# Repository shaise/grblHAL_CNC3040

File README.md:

# grblHAL_CNC3040 [WIP]
Hardware implementation of the grblHAL driver to work with Chinese CNC3040 type of machines  

This project is intended to upgrade any cnc machine that is controlled via parallel port such as the popular chinese CNC3040.  
Instead of having a dedicated LinuxCNC PC or mach32, This device connects directly to the CNC's controller, and can be controlled using any grbl Sender sw via USB connection or even WiFi!  
This device supports an optional stand-alone KeyPad, that is also included in this project.  

This project is based on the great work of @terjeio and his [GrblHAL](https://github.com/grblHAL) project. Thanks!

## Some images:

## Driver and KeyPad Assembly:
For instructions how to assemble, program and use the devices refer to the Wiki.

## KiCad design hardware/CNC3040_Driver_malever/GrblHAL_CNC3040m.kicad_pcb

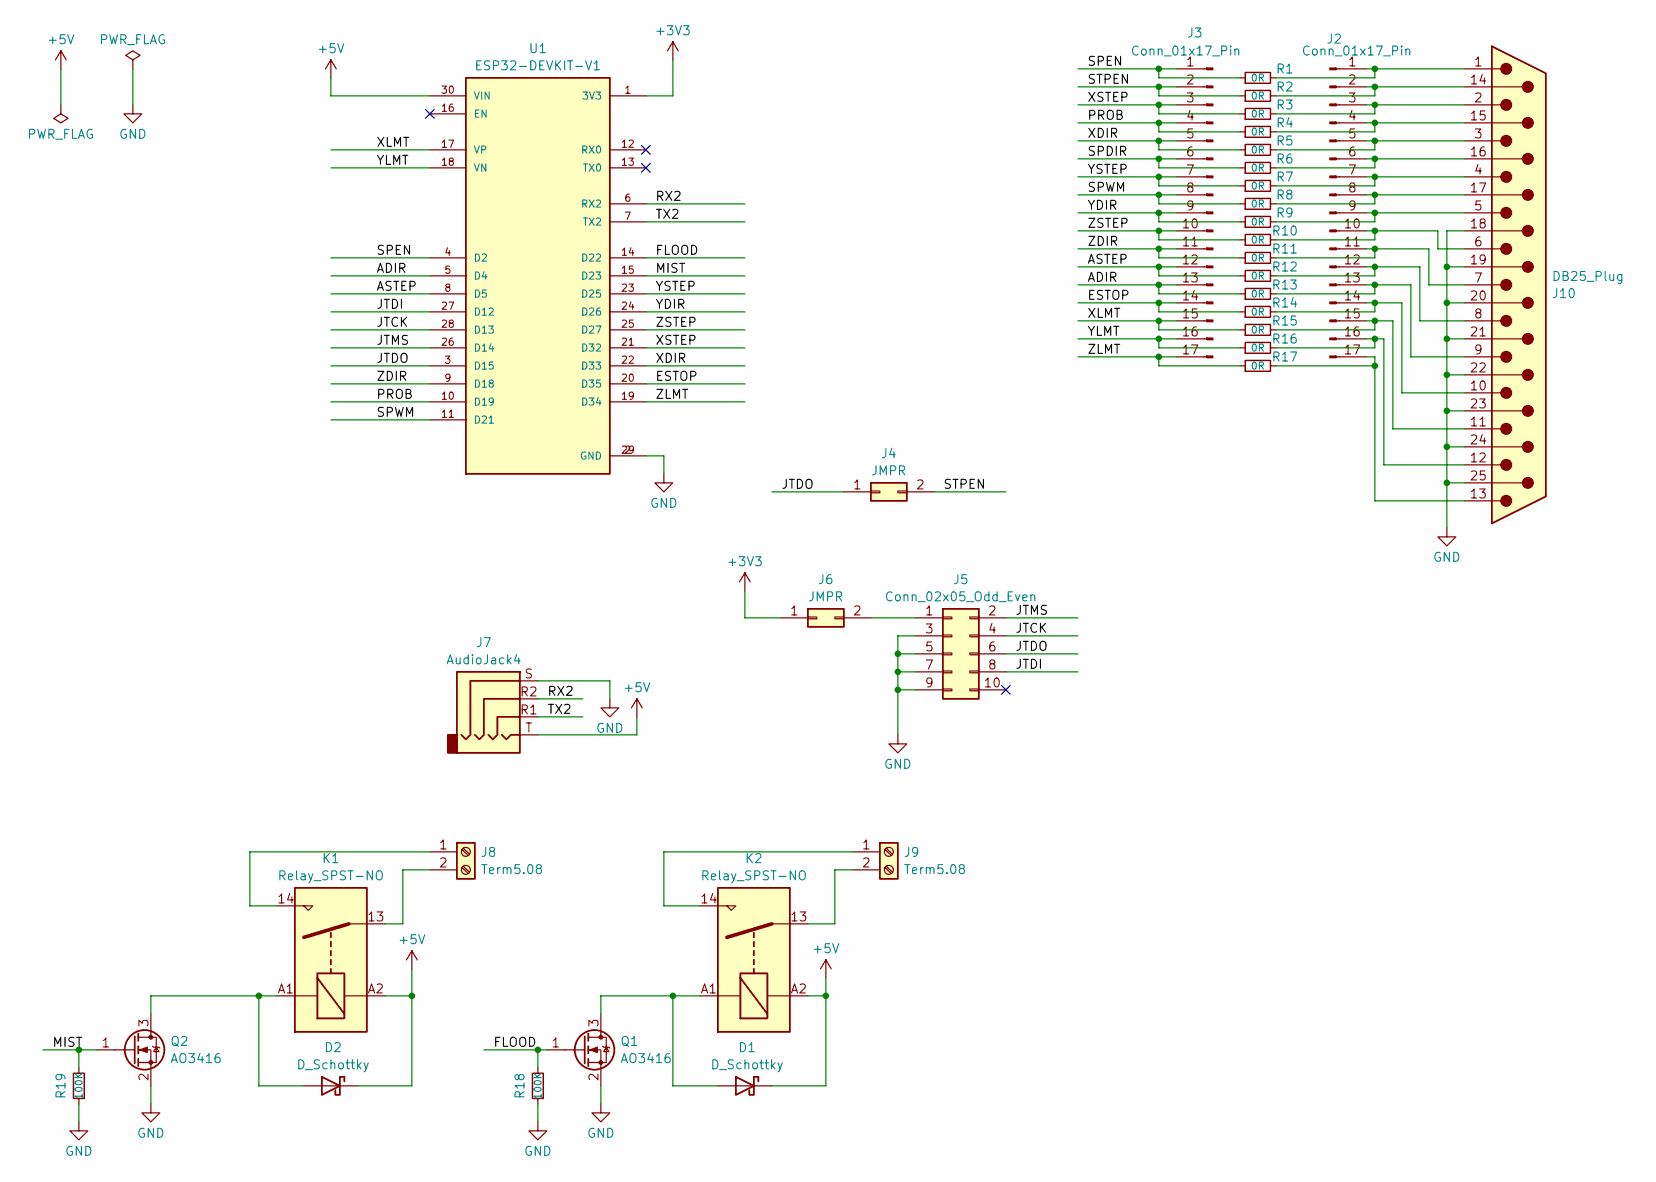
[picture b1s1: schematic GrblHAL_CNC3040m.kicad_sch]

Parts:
D1, D2: D_Schottky; D_SMA
J2, J3: Conn_01x17_Pin; PinHeader_1x17_P2.54mm_Vertical
J4, J6: JMPR; PinHeader_1x02_P2.54mm_Vertical
J5: Conn_02x05_Odd_Even; IDC-Header_2x05_P2.54mm_Vertical
J7: AudioJack4; Jack_3.5mm_PJ-320A
J8, J9: Term5.08; TerminalBlock_Phoenix_MKDS-1,5-2-5.08_1x02_P5.08mm_Horizont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
J10: DB25_Plug; DSUB-25_Male_Horizontal_P2.77x2.84mm_EdgePinOffset4.94mm_Ho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
K1, K2: Relay_SPST-NO; Relay_HF32FV-G
Q1, Q2: AO3416; SOT-23-3
R1, R2, R3, R4, R5, R6, R7, R8, R9, R10, R11, R12, R13, R14, R15, R16, R17: 0R; R_0603_1608Metric
R18, R19: 100K; R_0603_1608Metric
U1: ESP32-DEVKIT-V1; MODULE_ESP32_DEVKIT_V1; PARTREV N/A

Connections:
+3V3: J6.1, U1.1 (3V3)
+5V: D1.1 (K), D2.1 (K), J7.T, K1.A2, K2.A2, U1.30 (VIN)
/ADIR: J3.13, R13.1, U1.5 (D4)
/ASTEP: J3.12, R12.1, U1.8 (D5)
/ESTOP: J3.14, R14.1, U1.20 (D35)
/FLOOD: Q1.1 (G), R18.2, U1.14 (D22)
/JTCK: J5.4, U1.28 (D13)
/JTDI: J5.8, U1.27 (D12)
/JTDO: J4.1, J5.6, U1.3 (D15)
/JTMS: J5.2, U1.26 (D14)
/MIST: Q2.1 (G), R19.2, U1.15 (D23)
/PROB: J3.4, R4.1, U1.10 (D19)
/RX2: J7.R2, U1.6 (RX2)
/SPDIR: J3.6, R6.1
/SPEN: J3.1, R1.1, U1.4 (D2)
/SPWM: J3.8, R8.1, U1.11 (D21)
/STPEN: J3.2, J4.2, R2.1
/TX2: J7.R1, U1.7 (TX2)
/XDIR: J3.5, R5.1, U1.22 (D33)
/XLMT: J3.15, R15.1, U1.17 (VP)
/XSTEP: J3.3, R3.1, U1.21 (D32)
/YDIR: J3.9, R9.1, U1.24 (D26)
/YLMT: J3.16, R16.1, U1.18 (VN)
/YSTEP: J3.7, R7.1, U1.23 (D25)
/ZDIR: J3.11, R11.1, U1.9 (D18)
/ZLMT: J3.17, R17.1, U1.19 (D34)
/ZSTEP: J3.10, R10.1, U1.25 (D27)
GND: J5.3, J5.5, J5.7, J5.9, J7.S, J10.18, J10.19, J10.20, J10.21, J10.22, J10.23, J10.24, J10.25, Q1.2 (S), Q2.2 (S), R18.1, R19.1, U1.2 (GND), U1.29 (GND)
unnamed: D1.2 (A), K2.A1, Q1.3 (D)
unnamed: D2.2 (A), K1.A1, Q2.3 (D)
unnamed: J2.1, J10.1, R1.2
unnamed: J2.3, J10.2, R3.2
unnamed: J2.5, J10.3, R5.2
unnamed: J2.7, J10.4, R7.2
unnamed: J2.9, J10.5, R9.2
unnamed: J2.10, J10.6, R10.2
unnamed: J2.11, J10.7, R11.2
unnamed: J2.12, J10.8, R12.2
unnamed: J2.13, J10.9, R13.2
unnamed: J2.14, J10.10, R14.2
unnamed: J2.15, J10.11, R15.2
unnamed: J2.16, J10.12, R16.2
unnamed: J2.17, J10.13, R17.2
unnamed: J5.1, J6.2
unnamed: J8.1, K1.14
unnamed: J8.2, K1.13
unnamed: J9.1, K2.14
unnamed: J9.2, K2.13
unnamed: J2.2, J10.14, R2.2
unnamed: J2.4, J10.15, R4.2
unnamed: J2.6, J10.16, R6.2
unnamed: J2.8, J10.17, R8.2

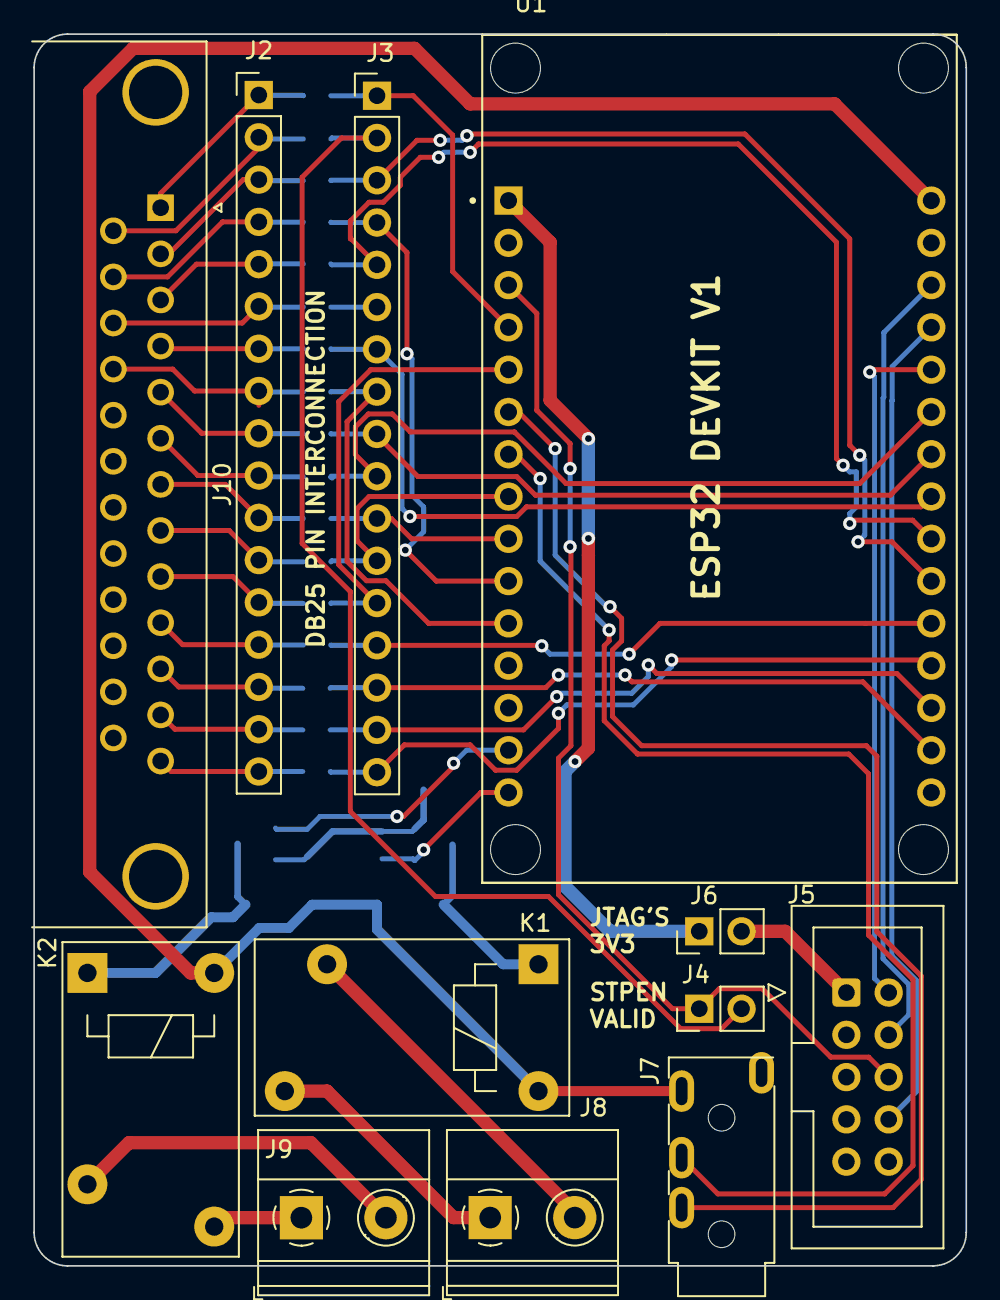
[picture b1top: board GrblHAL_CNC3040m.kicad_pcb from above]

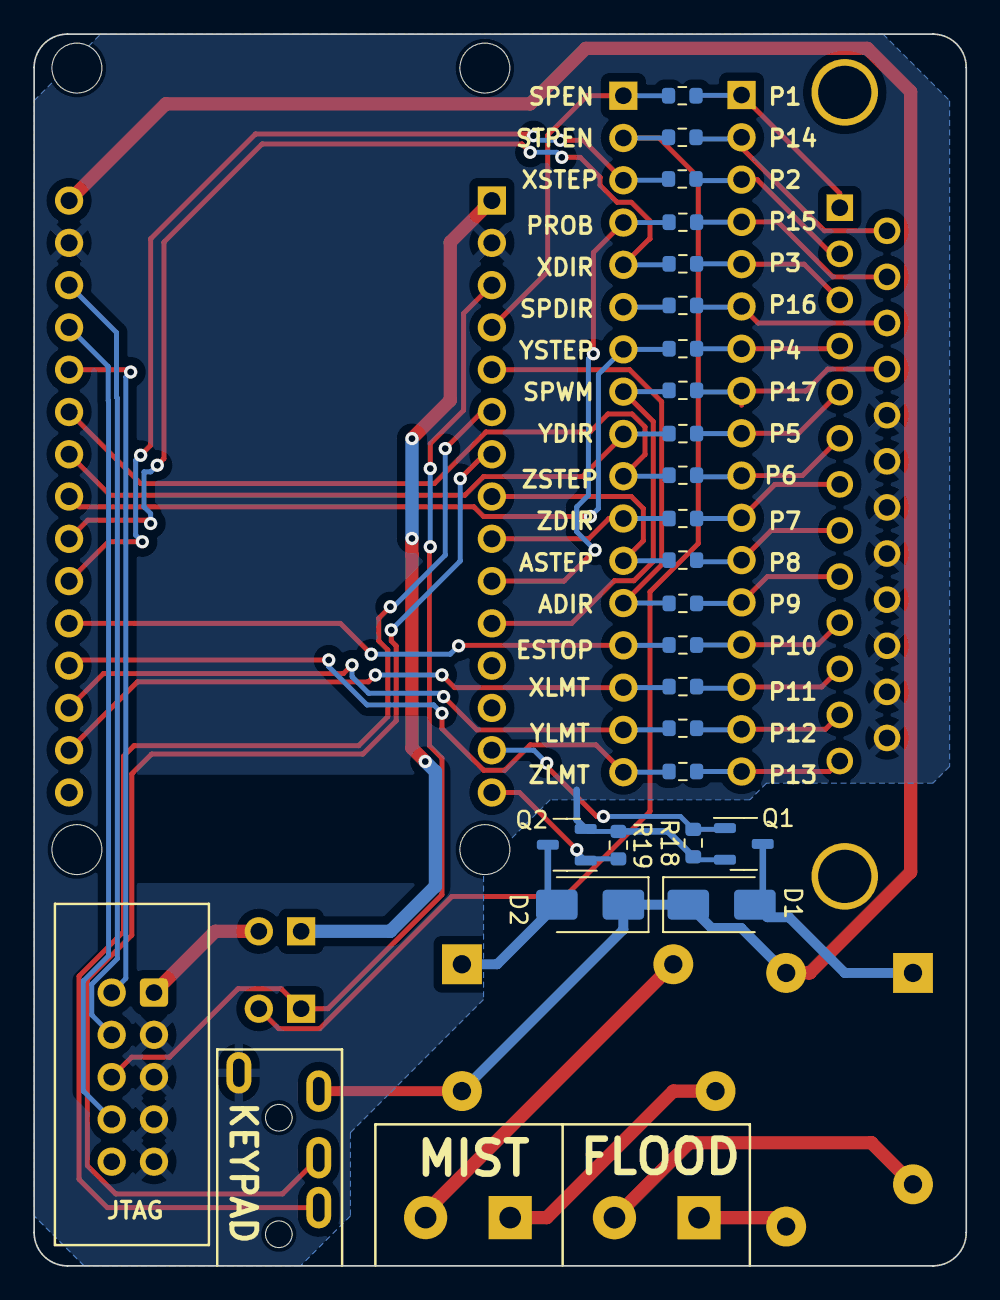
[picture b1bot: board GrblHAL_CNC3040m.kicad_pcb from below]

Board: 2 copper layers, 56.0 x 74.0 mm, 35 parts (23 on the bottom side), 52 nets.

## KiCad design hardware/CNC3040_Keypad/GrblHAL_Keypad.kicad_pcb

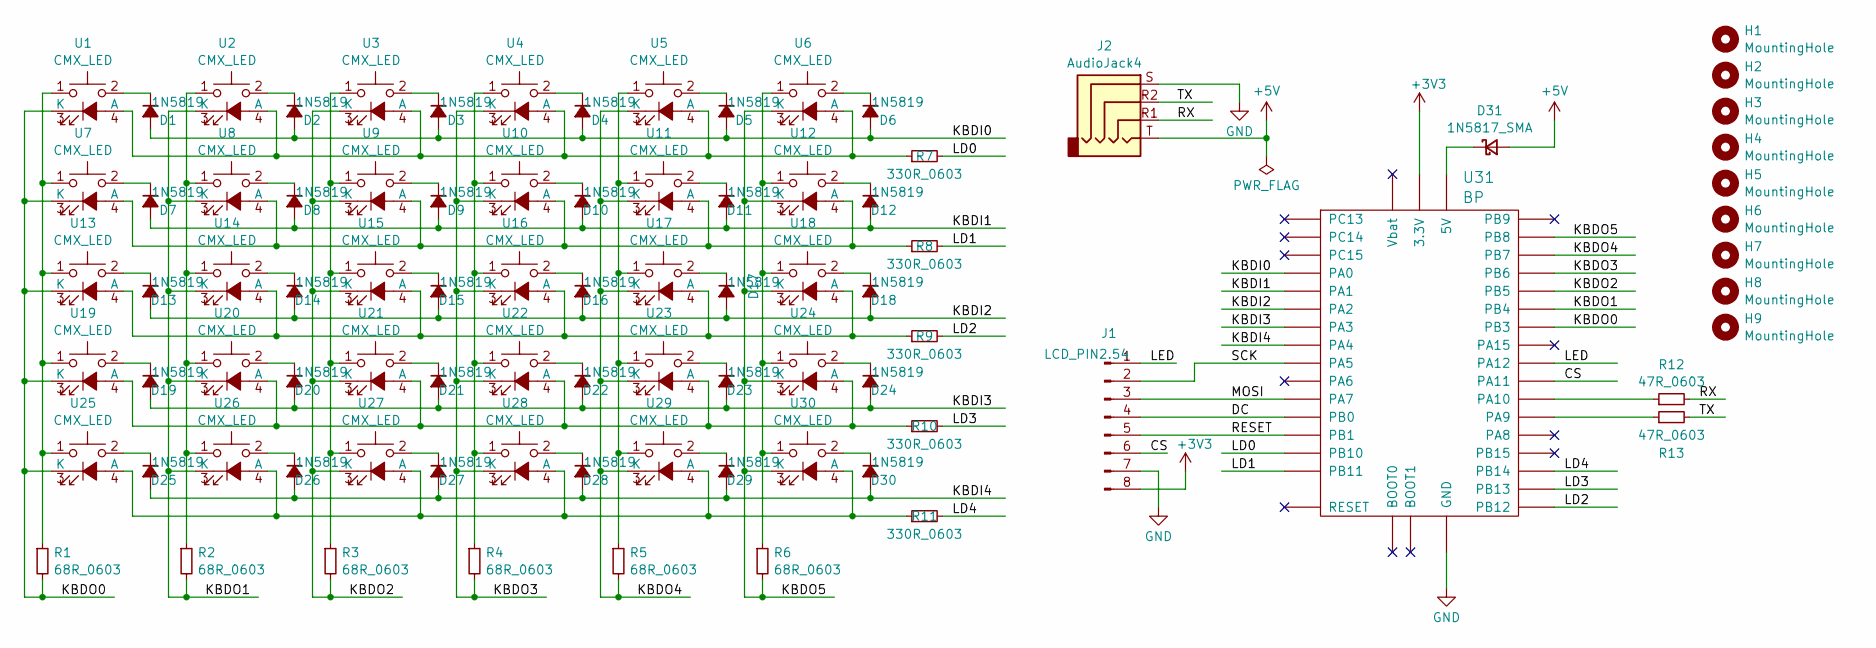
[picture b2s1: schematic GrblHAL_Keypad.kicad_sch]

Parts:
D1, D2, D3, D4, D5, D6, D7, D8, D9, D10, D11, D12, D13, D14, D15, D16, D17, D18, D19, D20, D21, D22, D23, D24, D25, D26, D27, D28, D29, D30: 1N5819; D_SOD-123
D31: 1N5817_SMA; D_SMA
H1, H2, H3, H4, H5, H6, H7, H8, H9: MountingHole; MountingHole_3.2mm_M3
J1: LCD_PIN2.54; PinHeader_1x08_P2.54mm_Vertical
J2: AudioJack4; Jack_3.5mm_PJ-320A
R1, R2, R3, R4, R5, R6: 68R_0603; R_0603_1608Metric
R7, R8, R9, R10, R11: 330R_0603; R_0603_1608Metric
R12, R13: 47R_0603; R_0603_1608Metric
U1, U2, U3, U4, U5, U6, U7, U8, U9, U10, U11, U12, U13, U14, U15, U16, U17, U18, U19, U20, U21, U22, U23, U24, U25, U26, U27, U28, U29, U30: CMX_LED; CherryMX_1.00u_KailhSocket_LED
U31: BP; BLUEPILL-BARE

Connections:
+3V3: J1.8, U31.3V3 (3.3V)
+5V: D31.2 (A), J2.T
/CS: J1.6, U31.PA11
/DC: J1.4, U31.PB0
/KBDI0: D1.2 (A), D2.2 (A), D3.2 (A), D4.2 (A), D5.2 (A), D6.2 (A), U31.PA0
/KBDI1: D7.2 (A), D8.2 (A), D9.2 (A), D10.2 (A), D11.2 (A), D12.2 (A), U31.PA1
/KBDI2: D13.2 (A), D14.2 (A), D15.2 (A), D16.2 (A), D17.2 (A), D18.2 (A), U31.PA2
/KBDI3: D19.2 (A), D20.2 (A), D21.2 (A), D22.2 (A), D23.2 (A), D24.2 (A), U31.PA3
/KBDI4: D25.2 (A), D26.2 (A), D27.2 (A), D28.2 (A), D29.2 (A), D30.2 (A), U31.PA4
/KBDO0: R1.2, U1.3 (K), U7.3 (K), U13.3 (K), U19.3 (K), U25.3 (K), U31.PB3
/KBDO1: R2.2, U2.3 (K), U8.3 (K), U14.3 (K), U20.3 (K), U26.3 (K), U31.PB4
/KBDO2: R3.2, U3.3 (K), U9.3 (K), U15.3 (K), U21.3 (K), U27.3 (K), U31.PB5
/KBDO3: R4.2, U4.3 (K), U10.3 (K), U16.3 (K), U22.3 (K), U28.3 (K), U31.PB6
/KBDO4: R5.2, U5.3 (K), U11.3 (K), U17.3 (K), U23.3 (K), U29.3 (K), U31.PB7
/KBDO5: R6.2, U6.3 (K), U12.3 (K), U18.3 (K), U24.3 (K), U30.3 (K), U31.PB8
/LD0: R7.2, U31.PB10
/LD1: R8.2, U31.PB11
/LD2: R9.2, U31.PB12
/LD3: R10.2, U31.PB13
/LD4: R11.2, U31.PB14
/LED: J1.1, U31.PA12
/MOSI: J1.3, U31.PA7
/RESET: J1.5, U31.PB1
/RX: J2.R1, R12.2
/SCK: J1.2, U31.PA5
/TX: J2.R2, R13.2
GND: J1.7, J2.S, U31.G (GND)
unnamed: D1.1 (K), U1.2
unnamed: D2.1 (K), U2.2
unnamed: D3.1 (K), U3.2
unnamed: D4.1 (K), U4.2
unnamed: D5.1 (K), U5.2
unnamed: D6.1 (K), U6.2
unnamed: D7.1 (K), U7.2
unnamed: D8.1 (K), U8.2
unnamed: D9.1 (K), U9.2
unnamed: D10.1 (K), U10.2
unnamed: D11.1 (K), U11.2
unnamed: D12.1 (K), U12.2
unnamed: D13.1 (K), U13.2
unnamed: D14.1 (K), U14.2
unnamed: D15.1 (K), U15.2
unnamed: D16.1 (K), U16.2
unnamed: D17.1 (K), U17.2
unnamed: D18.1 (K), U18.2
unnamed: D19.1 (K), U19.2
unnamed: D20.1 (K), U20.2
unnamed: D21.1 (K), U21.2
unnamed: D22.1 (K), U22.2
unnamed: D23.1 (K), U23.2
unnamed: D24.1 (K), U24.2
unnamed: D25.1 (K), U25.2
unnamed: D26.1 (K), U26.2
unnamed: D27.1 (K), U27.2
unnamed: D28.1 (K), U28.2
unnamed: D29.1 (K), U29.2
unnamed: D30.1 (K), U30.2
unnamed: D31.1 (K), U31.5V
unnamed: R1.1, U1.1, U7.1, U13.1, U19.1, U25.1
unnamed: R2.1, U2.1, U8.1, U14.1, U20.1, U26.1
unnamed: R3.1, U3.1, U9.1, U15.1, U21.1, U27.1
unnamed: R4.1, U4.1, U10.1, U16.1, U22.1, U28.1
unnamed: R5.1, U5.1, U11.1, U17.1, U23.1, U29.1
unnamed: R6.1, U6.1, U12.1, U18.1, U24.1, U30.1
unnamed: R12.1, U31.PA10
unnamed: R13.1, U31.PA9
unnamed: R7.1, U1.4 (A), U2.4 (A), U3.4 (A), U4.4 (A), U5.4 (A), U6.4 (A)
unnamed: R8.1, U7.4 (A), U8.4 (A), U9.4 (A), U10.4 (A), U11.4 (A), U12.4 (A)
unnamed: R9.1, U13.4 (A), U14.4 (A), U15.4 (A), U16.4 (A), U17.4 (A), U18.4 (A)
unnamed: R10.1, U19.4 (A), U20.4 (A), U21.4 (A), U22.4 (A), U23.4 (A), U24.4 (A)
unnamed: R11.1, U25.4 (A), U26.4 (A), U27.4 (A), U28.4 (A), U29.4 (A), U30.4 (A)

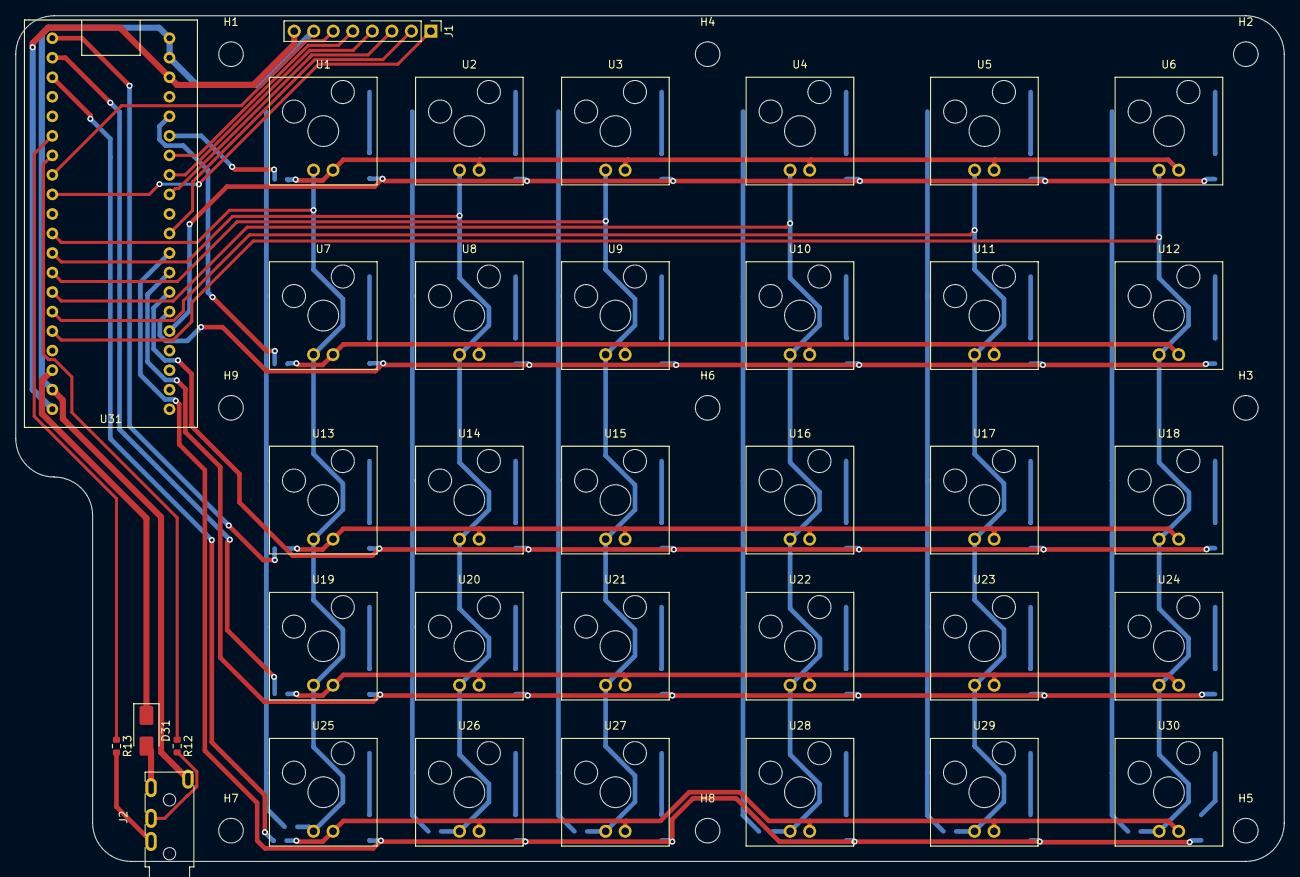
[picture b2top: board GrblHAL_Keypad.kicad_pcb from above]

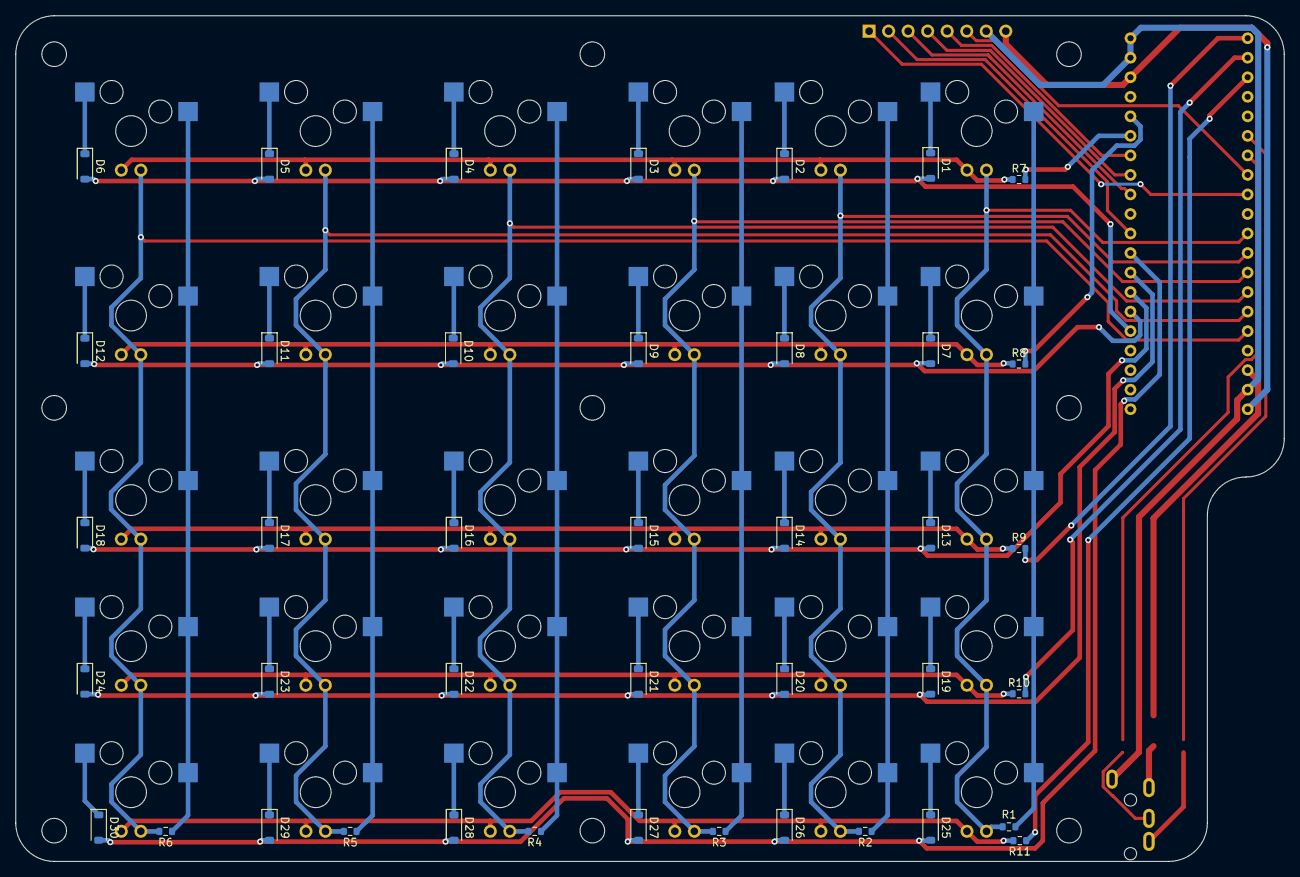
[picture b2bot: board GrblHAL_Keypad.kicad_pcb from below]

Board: 2 copper layers, 165.0 x 110.0 mm, 86 parts (41 on the bottom side), 71 nets.

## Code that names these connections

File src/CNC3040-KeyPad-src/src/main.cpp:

#include <Arduino.h>
#include "key_defs.h"

const uint8_t input_ios[] = {PA0, PA1, PA2, PA3, PA4};
const uint8_t output_ios[] = {PB3, PB4, PB5, PB6, PB7, PB8, PB10, PB11, PB12, PB13, PB14};
#define NUM_INPUTS sizeof(input_ios)
#define NUM_OUTPUTS sizeof(output_ios)

// scan from PB3 to PB8 
#define SCAN_START (1<<3)
#define SCAN_END   (1<<8)
#define SCAN_OUT_MASK 0x1F8
#define SCAN_IN_MASK 0x1F
#define SCAN_LED_MASK 0x7C00
int line_shift = SCAN_START; 
int line_count = 0;

uint32_t last_but_state, cur_but_state = 0;
uint32_t led_state = 0;
uint32_t last_millis = 0, cur_millis;

void setup() {
  Serial.begin(115200);
  Serial1.begin(115200);
  for (int i = 0; i < NUM_INPUTS; i++)
    pinMode(input_ios[i], INPUT_PULLUP);
  for (int i = 0; i < NUM_OUTPUTS; i++)
    pinMode(output_ios[i], OUTPUT);
  //GPIOB->ODR = SCAN_LED_MASK;
}

uint32_t presslap;

void SendCmd(uint8_t cmd)
{
  Serial1.write(cmd);
  //Serial.println(cmd, 16);
}

void HandleDirectMap(const uint32_t *map, int press_mask)
{
  while (*map != 0)
  {
    uint32_t key = *map++;
    uint8_t cmd = (uint8_t)*map++;
    if (press_mask & key)
      SendCmd(cmd);
  }
}

void HandleKeyPressed(int press_mask)
{
  #define IF_PRESSED(x) if (press_mask & (x))
  if (press_mask == 0)
    return;
  presslap = millis();
  HandleDirectMap(jog_key_map, press_mask);
  HandleDirectMap(motion_key_map, press_mask);
  HandleDirectMap(control_key_map, press_mask);

}

void HandleKeyReleased(int release_mask)
{
  #define IF_RELEASED(x) if (press_mask & (x))
  if (release_mask == 0)
    return;
  
  //Serial.println(millis()-presslap);
  // any key release will cancel jog motion
  SendCmd(CMD_CANCL_JOG);
}


void poll_buttons_leds()
{
  int in, leds, shift;
  in = (int)GPIOA->IDR & SCAN_IN_MASK;
  shift = line_count * 5;
  cur_but_state &= ~(SCAN_IN_MASK << shift);
  cur_but_state |= (in ^ SCAN_IN_MASK) << shift;
  line_shift <<= 1;
  line_count++;
  if (line_count >= 6)
  {
    line_shift = SCAN_START;
    line_count = 0;
  }
  GPIOB->BRR = SCAN_LED_MASK;
  shift = line_count * 5;
  leds = (led_state >> shift) & 0x1F;
  GPIOB->BSRR = SCAN_OUT_MASK | leds << 10;
  //GPIOB->BSRR = leds << 10;
  GPIOB->BRR = line_shift;

  // look for key press/release
  if (cur_but_state != last_but_state)
  {
    //Serial.println((int)GPIOB->ODR & SCAN_LED_MASK, 16);
    //Serial.println(cur_but_state, 16);
    uint32_t changes = last_but_state ^ cur_but_state;
    HandleKeyPressed(changes & cur_but_state);
    HandleKeyReleased(changes & ~cur_but_state);
    last_but_state = cur_but_state;
    led_state = cur_but_state;
    //Serial1.write((uint8_t)0xA5);
  }

}



void loop() {
  cur_millis = millis();
  if (cur_millis == last_millis)
    return; 
  
  poll_buttons_leds();
  last_millis = cur_millis;

  if (Serial1.available())
  {
    Serial.print("Got: ");
    Serial.println((int)Serial1.read(), 16);
  }
}

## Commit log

2023-09-19 add bom
2024-01-23 add male version of the driver
